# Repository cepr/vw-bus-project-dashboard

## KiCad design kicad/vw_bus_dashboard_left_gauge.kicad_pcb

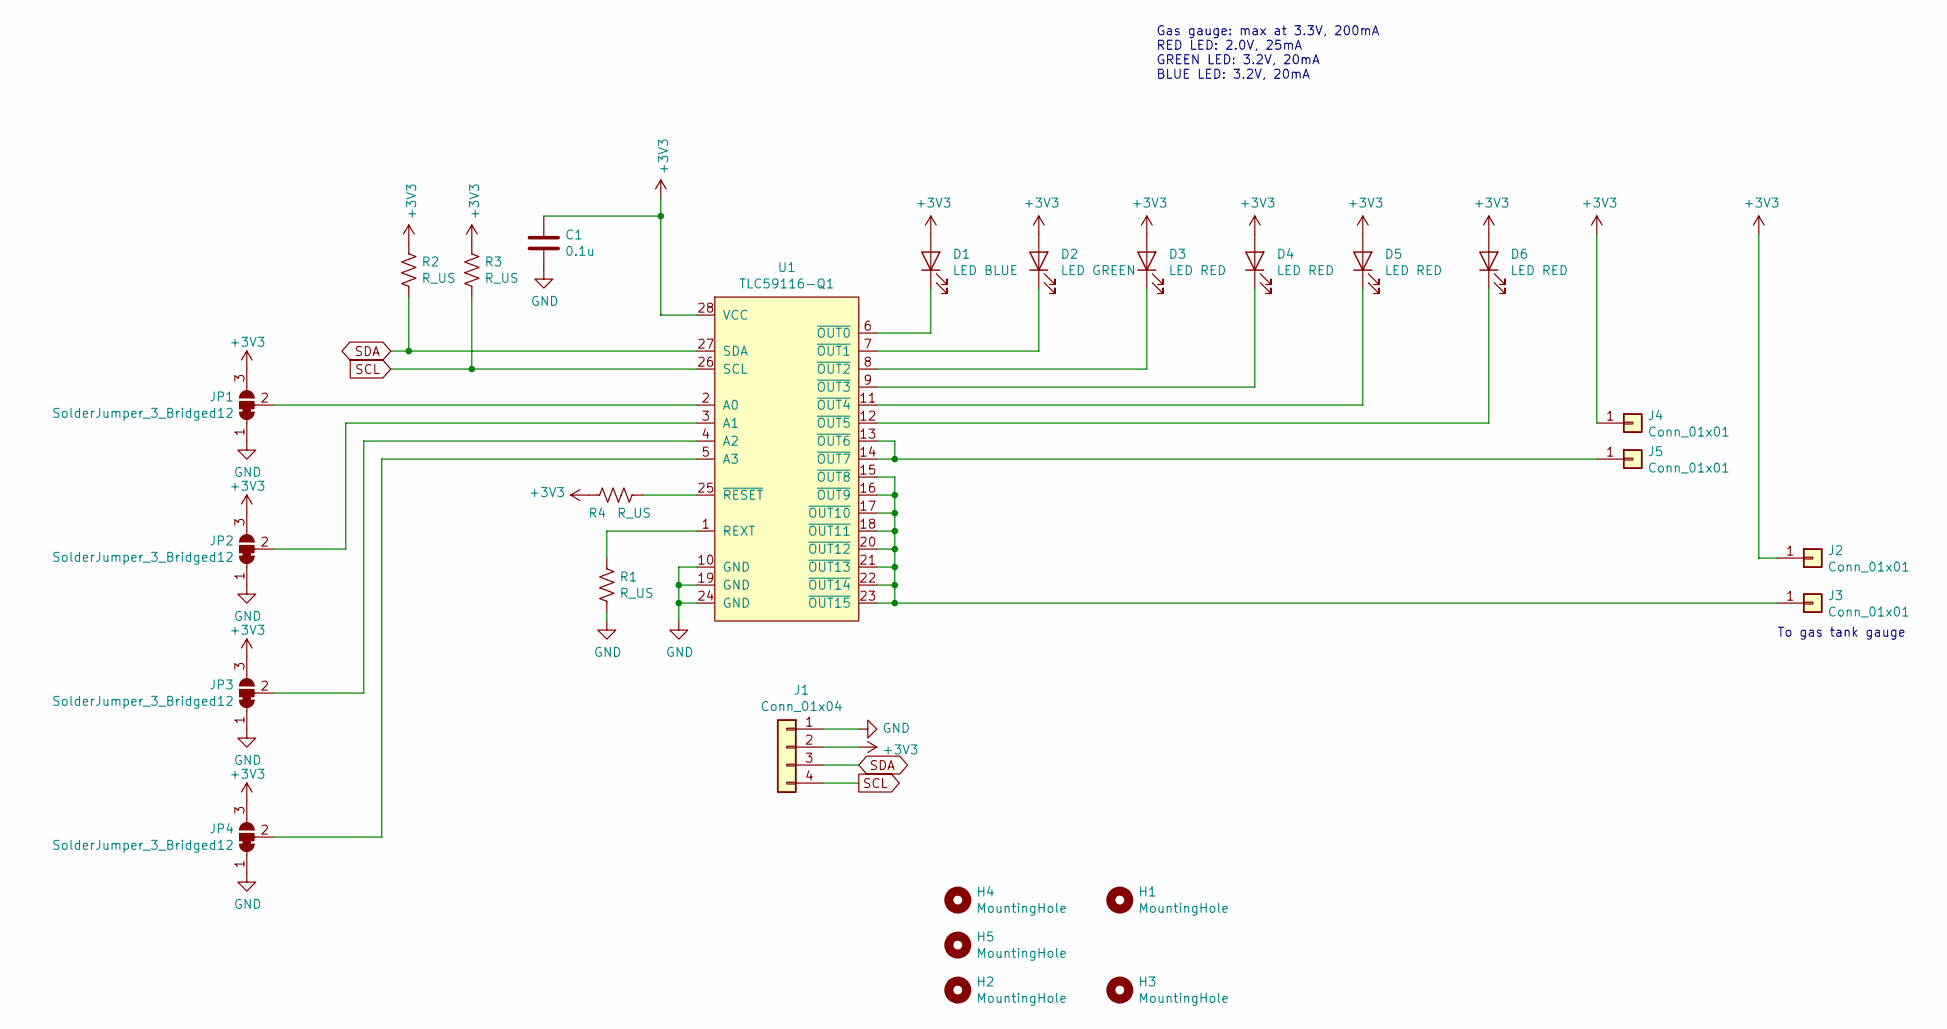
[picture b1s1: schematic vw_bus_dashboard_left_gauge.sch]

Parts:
C1: 0.1u; C_0805_2012Metric_Pad1.15x1.40mm_HandSolder
D1: LED BLUE; LED_D5.0mm; DigiKey 1080-1597-1-ND
D2: LED GREEN; LED_D5.0mm; DigiKey 1080-1597-1-ND
D3, D4: LED RED; LED_D5.0mm; DigiKey 1080-1597-1-ND
D5: LED RED; LED_D5.0mm; DigiKey 754-1890-ND
D6: LED RED; LED_D5.0mm; DigiKey 516-3974-1-ND
H1, H3: MountingHole; MountingHole_5.3mm_M5
H2, H4, H5: MountingHole; MountingHole_3.2mm_M3
J1: Conn_01x04; JST_SH_SM04B-SRSS-TB_1x04-1MP_P1.00mm_Horizontal
J2, J3, J4, J5: Conn_01x01; TestPoint_Pad_4.0x4.0mm
JP1, JP2, JP3, JP4: SolderJumper_3_Bridged12; SolderJumper-3_P1.3mm_Bridged12_RoundedPad1.0x1.5mm_NumberL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
R1, R2, R3, R4: R_US; R_0805_2012Metric_Pad1.15x1.40mm_HandSolder
U1: TLC59116-Q1; TSSOP-28_4.4x9.7mm_P0.65mm; DigiKey 296-44135-1-ND

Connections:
+3V3: C1.1, D1.2 (A), D2.2 (A), D3.2 (A), D4.2 (A), D5.2 (A), D6.2 (A), J1.2, J2.1, J4.1, JP1.3 (B), JP2.3 (B), JP3.3 (B), JP4.3 (B), R2.1, R3.1, R4.1, U1.28 (VCC)
GND: C1.2, J1.1, JP1.1 (A), JP2.1 (A), JP3.1 (A), JP4.1 (A), R1.2, U1.10 (GND), U1.19 (GND), U1.24 (GND)
unnamed: D1.1 (K), U1.6 (~OUT0)
unnamed: D2.1 (K), U1.7 (~OUT1)
unnamed: D3.1 (K), U1.8 (~OUT2)
unnamed: D4.1 (K), U1.9 (~OUT3)
unnamed: D5.1 (K), U1.11 (~OUT4)
unnamed: D6.1 (K), U1.12 (~OUT5)
unnamed: J3.1, U1.15 (~OUT8), U1.16 (~OUT9), U1.17 (~OUT10), U1.18 (~OUT11), U1.20 (~OUT12), U1.21 (~OUT13), U1.22 (~OUT14), U1.23 (~OUT15)
unnamed: J5.1, U1.13 (~OUT6), U1.14 (~OUT7)
unnamed: JP1.2 (C), U1.2 (A0)
unnamed: JP2.2 (C), U1.3 (A1)
unnamed: JP3.2 (C), U1.4 (A2)
unnamed: JP4.2 (C), U1.5 (A3)
unnamed: R1.1, U1.1 (REXT)
unnamed: R4.2, U1.25 (~RESET)
SCL: J1.4, R3.2, U1.26 (SCL)
SDA: J1.3, R2.2, U1.27 (SDA)

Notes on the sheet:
Gas gauge: max at 3.3V, 200mA RED LED: 2.0V, 25mA GREEN LED: 3.2V, 20mA BLUE LED: 3.2V, 20mA
To gas tank gauge

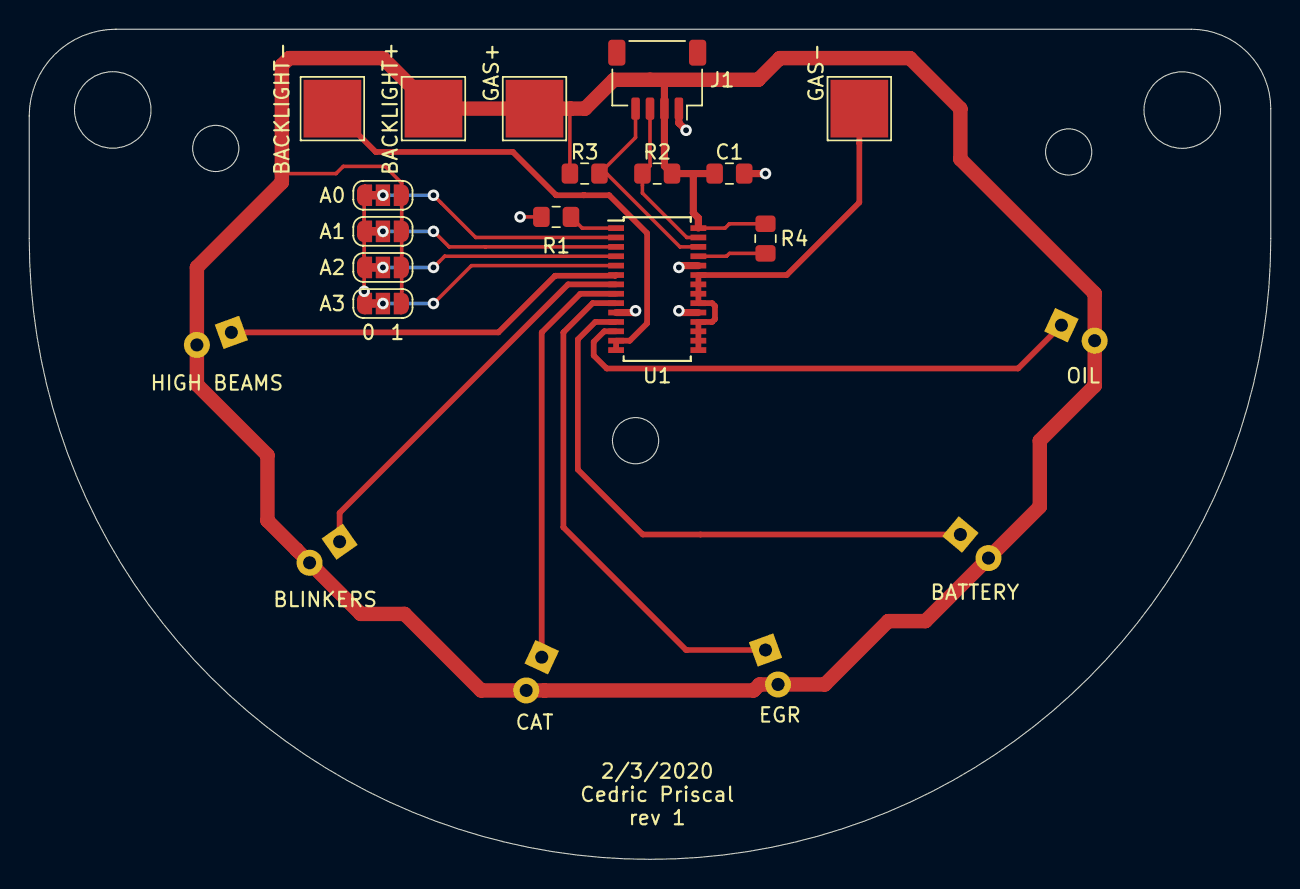
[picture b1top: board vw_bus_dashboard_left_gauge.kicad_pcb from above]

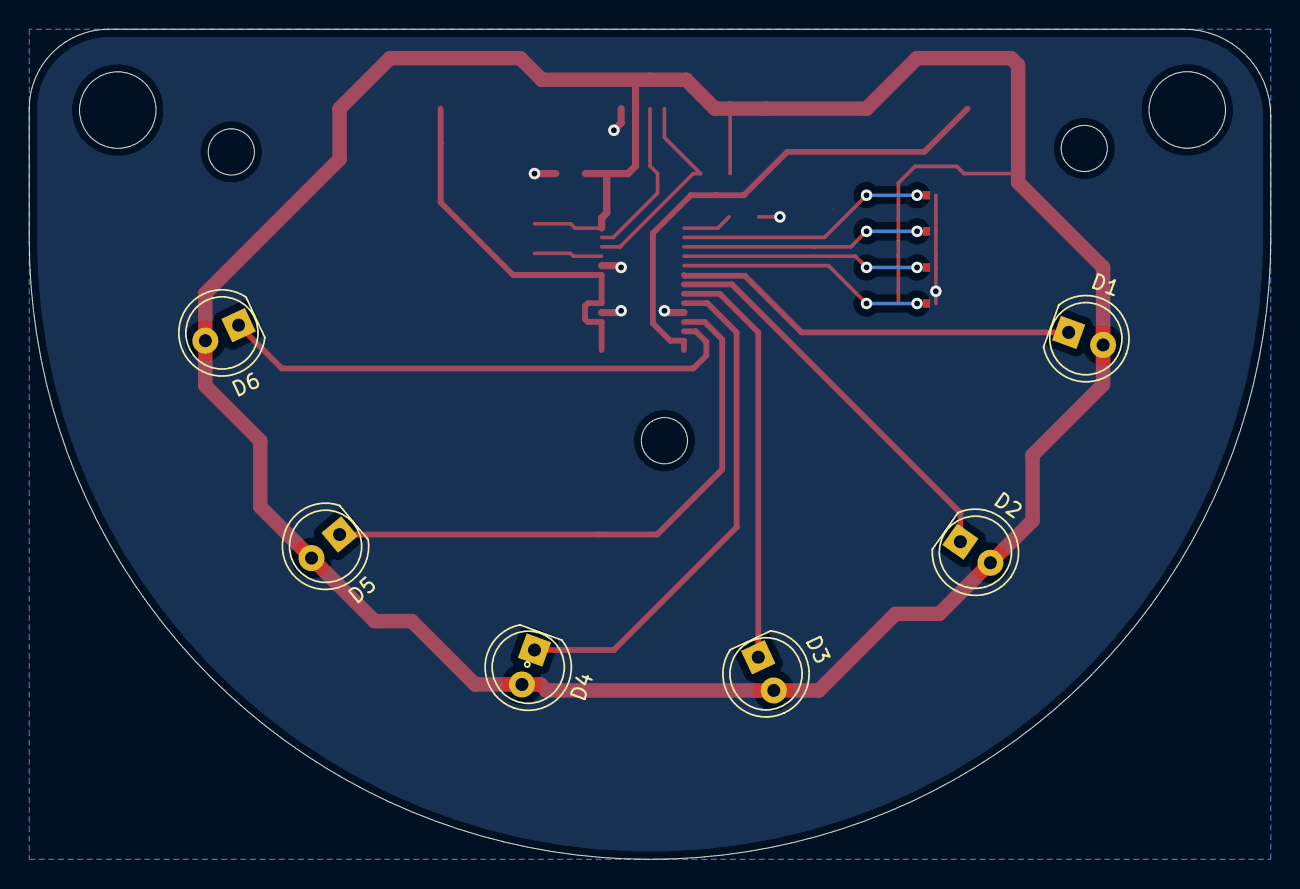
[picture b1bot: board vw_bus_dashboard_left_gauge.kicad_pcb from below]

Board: 2 copper layers, 86.0 x 57.5 mm, 26 parts (6 on the bottom side), 18 nets.

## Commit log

2020-02-04 rev 1
2020-02-05 Adding DigiKey product numbers
2022-03-04 Rev 2 using NeoPixels
